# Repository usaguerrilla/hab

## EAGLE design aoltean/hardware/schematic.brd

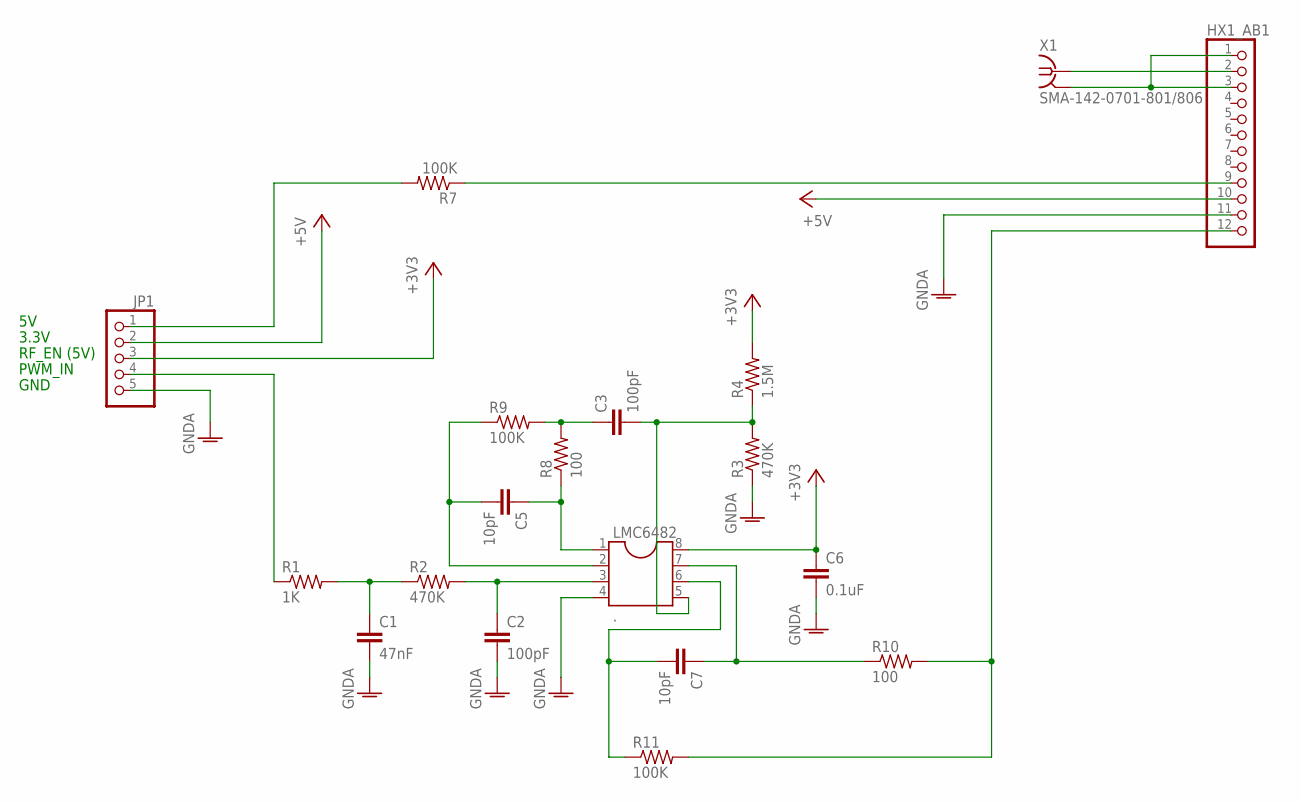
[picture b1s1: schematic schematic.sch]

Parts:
C1: 47nF; C2.5-2
C2, C3: 100pF; C2.5-2
C5, C7: 10pF; C2.5-2
C6: 0.1uF; C2.5-2
HX1_AB1: 1X12
JP1: 1X05
LMC6482: .; DIL08
R1: 1K; 0204V
R2, R3: 470K; 0204V
R4: 1.5M; 0204V
R7, R9, R11: 100K; 0204V
R8, R10: 100; 0204V
X1: SMA-142-0701-801/806; J502-ND-142-0701-801/806

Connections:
+3V3: C6.1, JP1.3, LMC6482.8, R4.2
+5V: HX1_AB1.10, JP1.2
GNDA: C1.2, C2.2, C6.2, HX1_AB1.11, JP1.5, LMC6482.4, R3.1
unnamed: JP1.4, R1.1
unnamed: C1.1, R1.2, R2.1
unnamed: C2.1, LMC6482.3, R2.2
unnamed: C7.2, LMC6482.6, R11.1
unnamed: C3.2, LMC6482.5, R3.2, R4.1
unnamed: C3.1, R8.2, R9.2
unnamed: HX1_AB1.2, X1.1
unnamed: HX1_AB1.1, HX1_AB1.3, X1.G@1 (2), X1.G@2 (2), X1.G@3 (2), X1.G@4 (2)
unnamed: HX1_AB1.9, R7.1
unnamed: C7.1, LMC6482.7, R10.1
unnamed: C5.1, LMC6482.1, R8.1
unnamed: HX1_AB1.12, R10.2, R11.2
unnamed: C5.2, LMC6482.2, R9.1
unnamed: JP1.1, R7.2

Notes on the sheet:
RF_EN (5V)
3.3V
PWM_IN
GND

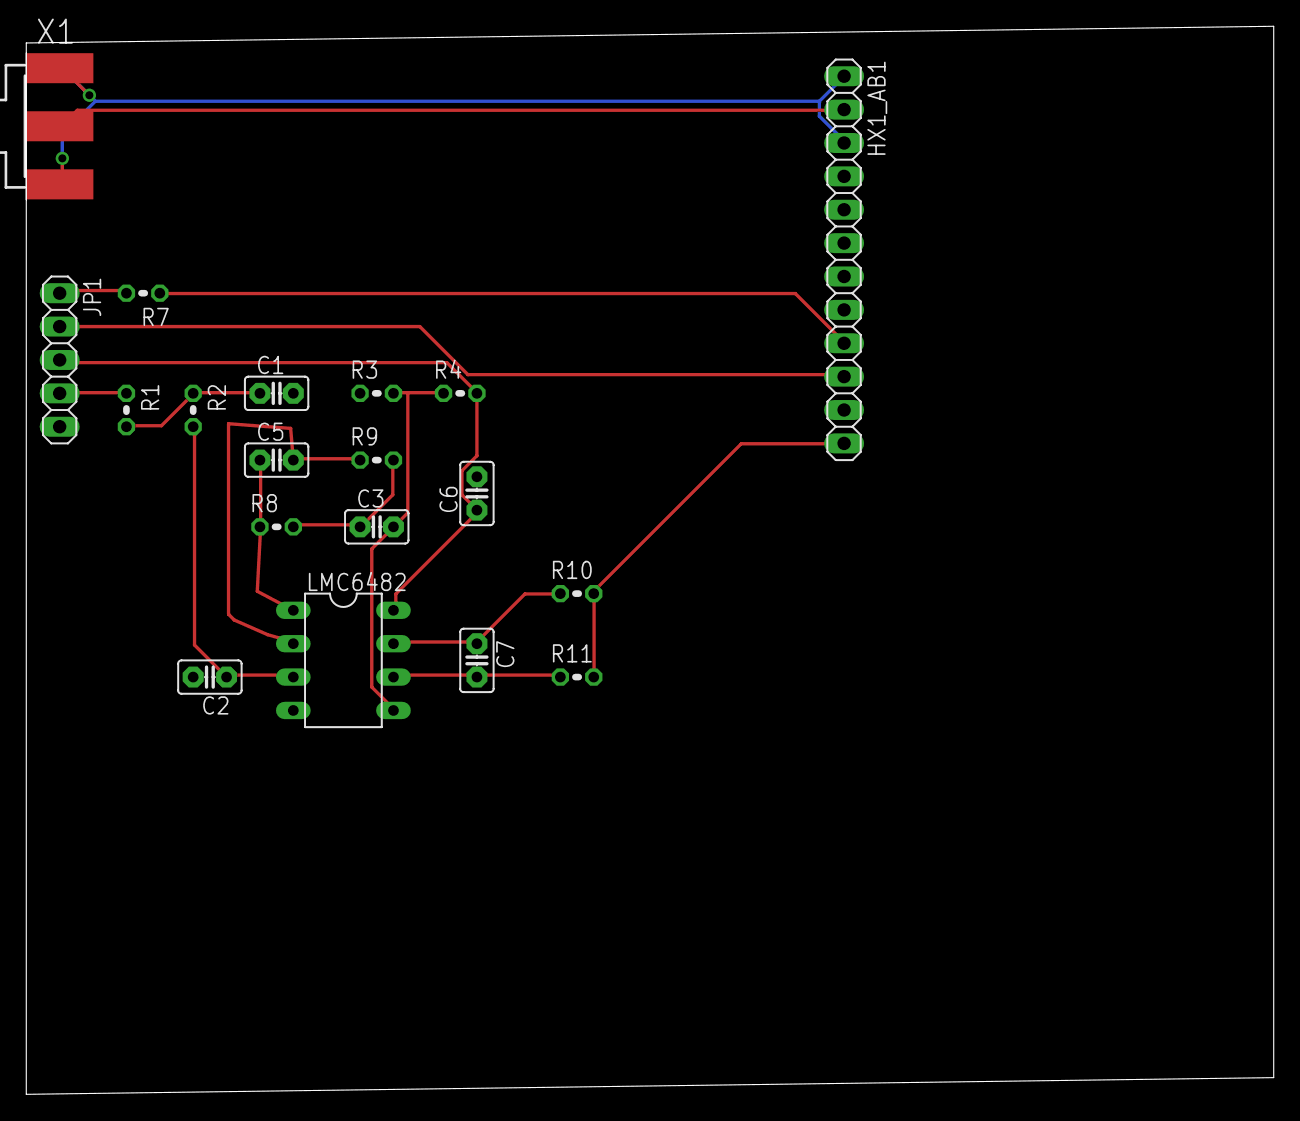
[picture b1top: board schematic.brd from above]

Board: 2 copper layers, 94.9 x 81.3 mm, 19 parts (0 on the bottom side), 17 nets.

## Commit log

2015-07-21 Add op-amp two stages
    - still messy (first-time Eagle user). Checked in early version.
